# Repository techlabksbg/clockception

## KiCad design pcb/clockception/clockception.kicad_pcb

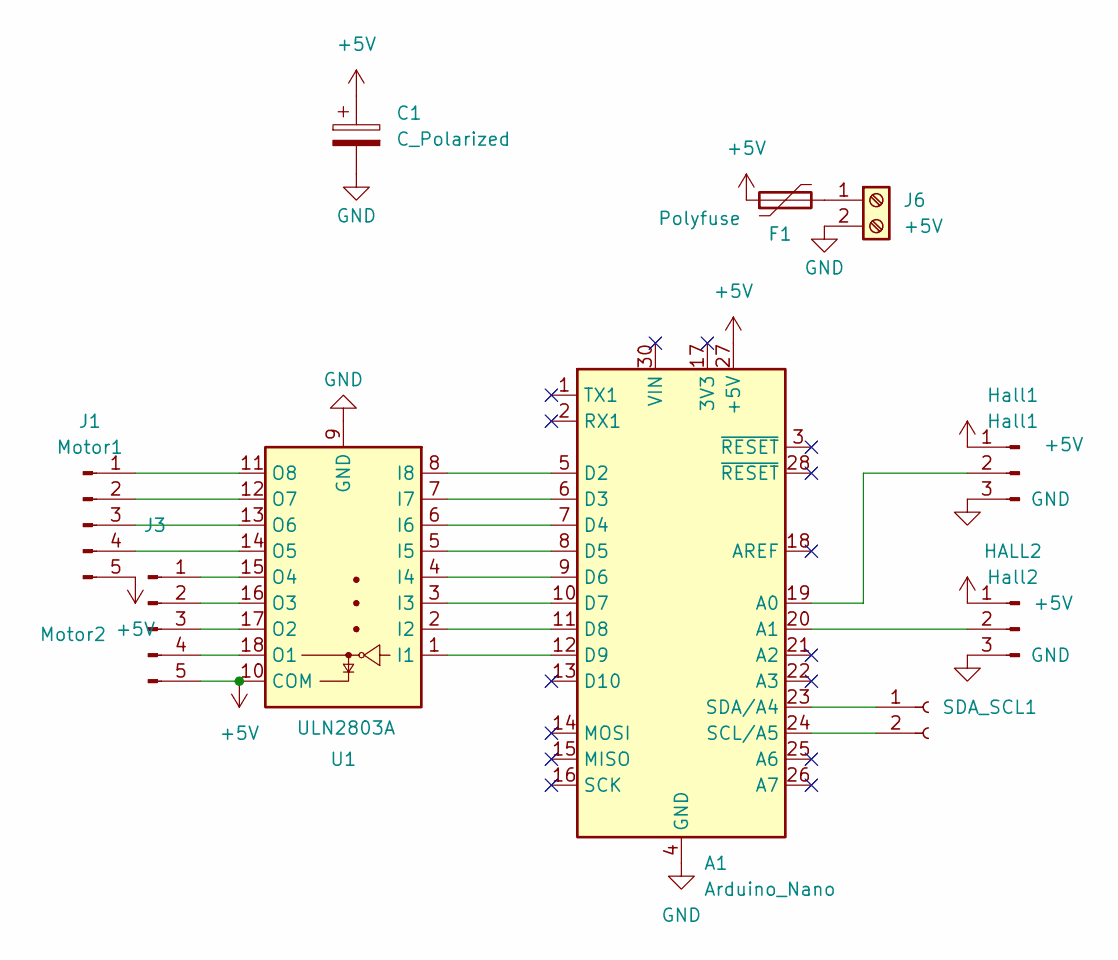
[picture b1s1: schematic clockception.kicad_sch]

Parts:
A1: Arduino_Nano
C1: C_Polarized; CP_Radial_D5.0mm_P2.00mm
F1: Polyfuse; Fuse_1812_4532Metric_Pad1.30x3.40mm_HandSolder
HALL2: Hall2; JST_XH_B3B-XH-A_1x03_P2.50mm_Vertical
Hall1: Hall1; JST_XH_B3B-XH-A_1x03_P2.50mm_Vertical
J1: Motor1; JST_XH_B5B-XH-A_1x05_P2.50mm_Vertical
J3: Motor2; JST_XH_B5B-XH-A_1x05_P2.50mm_Vertical
J6: +5V; TerminalBlock_CUI_TB007-508-02_1x02_P5.08mm_Horizontal
SDA_SCL1: JST_PH_B2B-PH-K_1x02_P2.00mm_Vertical
U1: ULN2803A; SOP-18_7.495x11.515mm_P1.27mm

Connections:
+5V: A1.27 (+5V), C1.1, F1.1, HALL2.1, Hall1.1, J1.5, J3.5, U1.10 (COM)
GND: A1.4 (GND), A1.29 (GND), C1.2, HALL2.3, Hall1.3, J6.2, U1.9 (GND)
unnamed: A1.19 (A0), Hall1.2
unnamed: A1.20 (A1), HALL2.2
unnamed: A1.5 (D2), U1.8 (I8)
unnamed: A1.6 (D3), U1.7 (I7)
unnamed: A1.7 (D4), U1.6 (I6)
unnamed: A1.8 (D5), U1.5 (I5)
unnamed: A1.9 (D6), U1.4 (I4)
unnamed: A1.10 (D7), U1.3 (I3)
unnamed: A1.11 (D8), U1.2 (I2)
unnamed: A1.12 (D9), U1.1 (I1)
unnamed 12: A1.24 (SCL/A5), SDA_SCL1.2; also elsewhere on the board
unnamed 13: A1.23 (SDA/A4), SDA_SCL1.1; also elsewhere on the board
unnamed: J1.1, U1.11 (O8)
unnamed: J1.2, U1.12 (O7)
unnamed: J1.3, U1.13 (O6)
unnamed: J1.4, U1.14 (O5)
unnamed: J3.1, U1.15 (O4)
unnamed: J3.2, U1.16 (O3)
unnamed: J3.3, U1.17 (O2)
unnamed: J3.4, U1.18 (O1)
unnamed: F1.2, J6.1

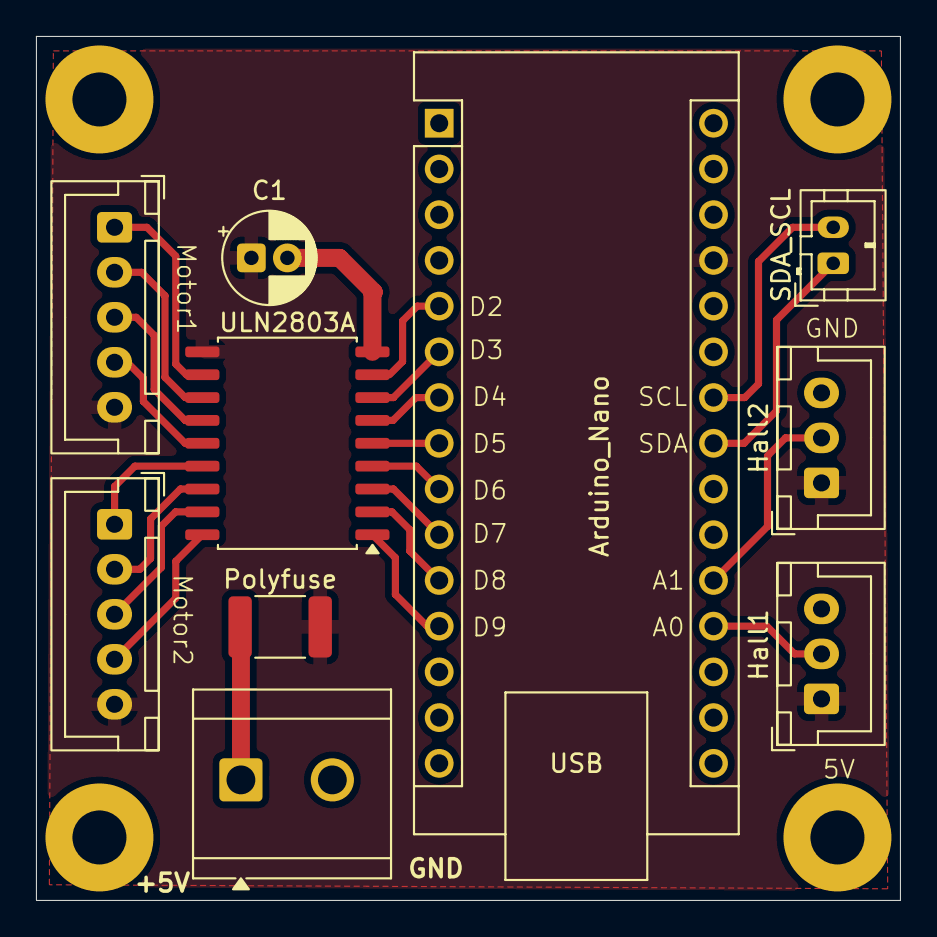
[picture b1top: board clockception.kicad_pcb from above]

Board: 2 copper layers, 48.0 x 48.0 mm, 10 parts (0 on the bottom side), 23 nets.

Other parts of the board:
SDA_SCL: JST_PH_B2B-PH-K_1x02_P2.00mm_Vertical

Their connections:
unnamed 12: SDA_SCL.2; also elsewhere on the board
unnamed 13: SDA_SCL.1; also elsewhere on the board
